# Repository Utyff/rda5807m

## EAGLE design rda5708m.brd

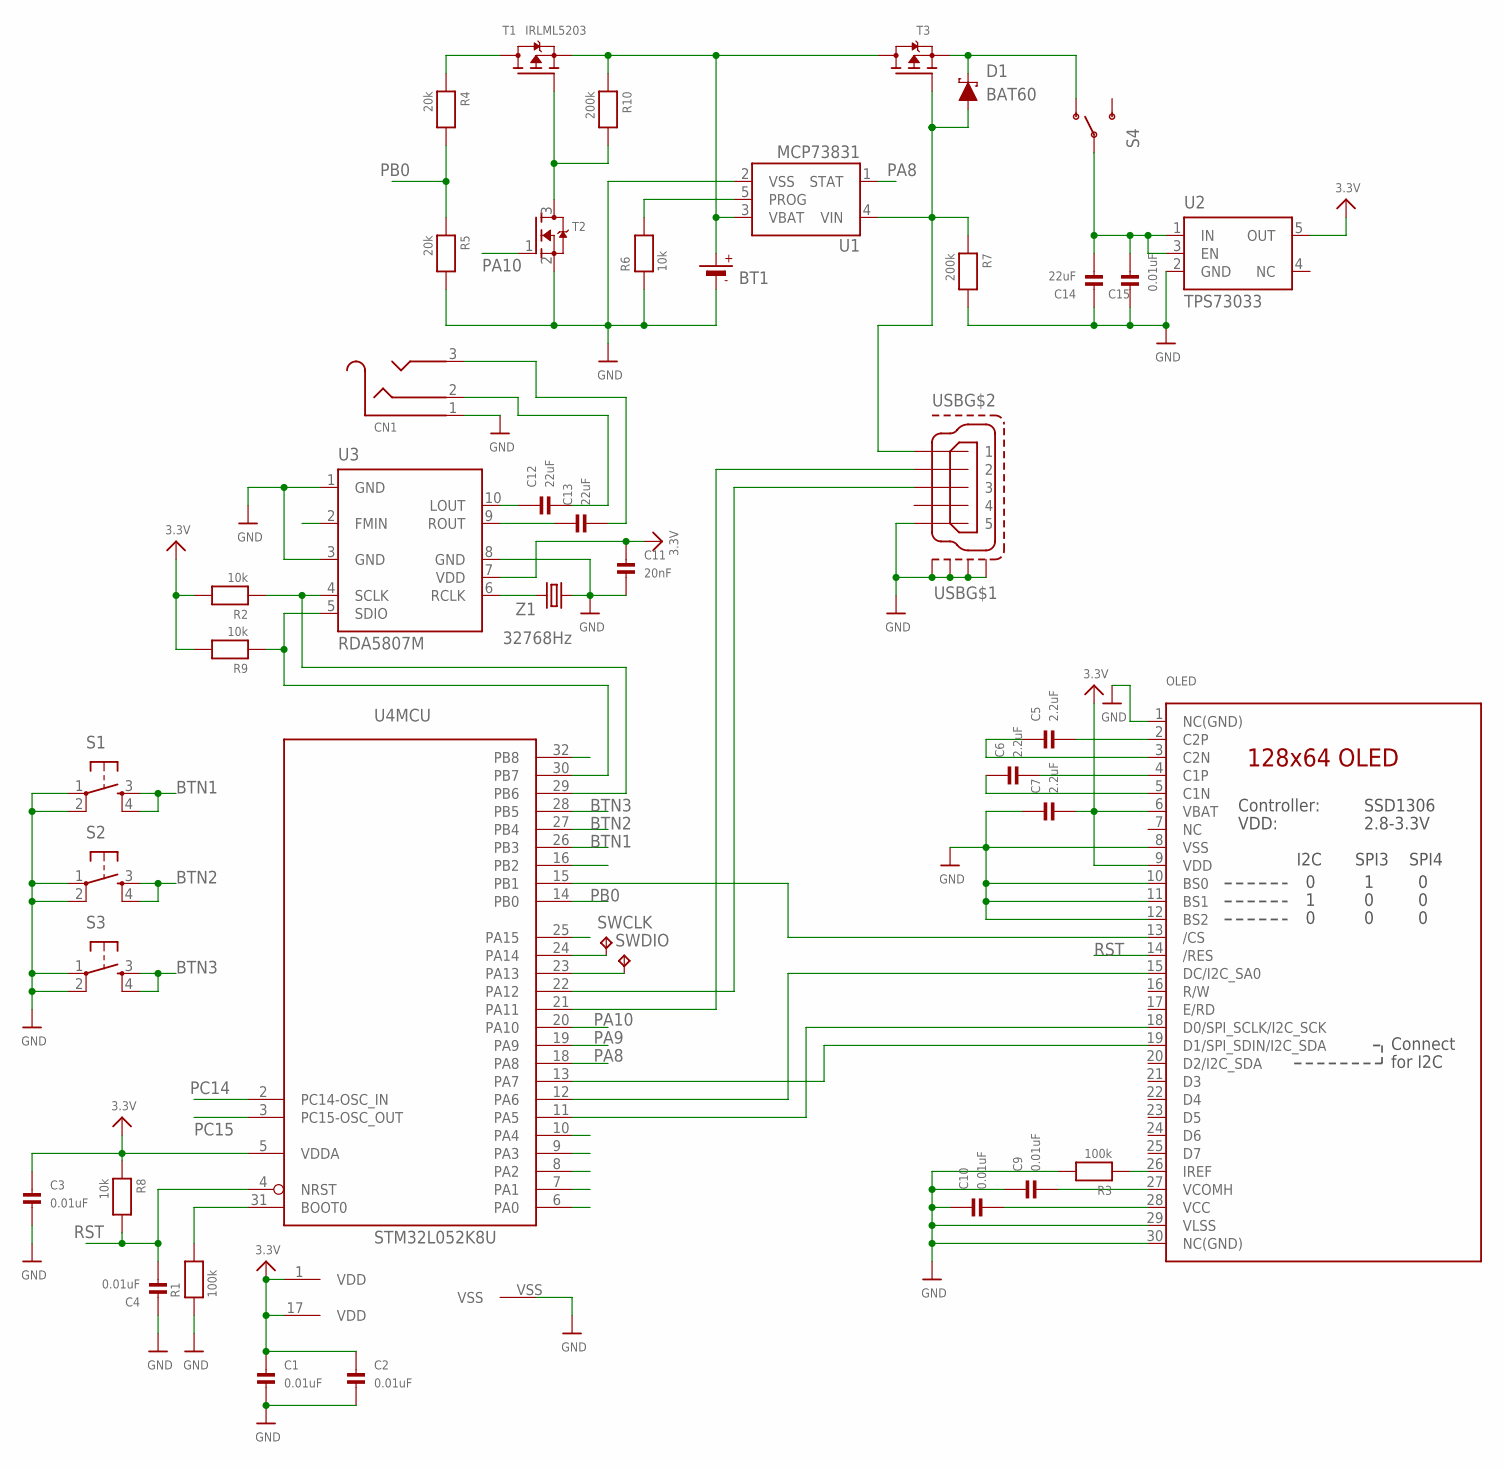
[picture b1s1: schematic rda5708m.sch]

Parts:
BT1: LiPo 4.2V; JSTPH2
C1, C2, C3, C4, C9, C10, C15: 0.01uF; 0603
C5, C6, C7: 2.2uF; 0603
C11: 20nF; 0603
C12, C13, C14: 22uF; 0805
CN1: AUDIO_3.5JACK; AUDIO_3.5
D1: BAT60; SOD-323
OLED: DISP_OLED_UG-2864HSWEG012SIDE; OLED0.96
R1, R3: 100k; 0603
R2, R6, R8, R9: 10k; 0603
R4, R5: 20k; 0603
R7, R10: 200k; 0603
S1, S2, S3: TAC_SWITCH; TACTILE-SWITCH-SMD45
S4: SWITCH-SPDTPTH2; SWITCH-DPDT
SWCLK: TPTP10R; TP10R
SWDIO: TPTP10R; TP10R
T1: IRLML5203; SOT23-R
T2: MOSFET-NREFLOW; SOT23-R
T3: MOSFET-P; SOT23-R
U1: MCP73831; SOT23-5
U2: TPS73033; SOT23-5
U3: RDA5807M; MSOP10
U4: STM32L052K8U; UFQFPN32
USB: MICRO-USB-SHIELD-MICRO_USB-B_4.85_HORN; MICRO_USB-B_4.85_HORN
Z1: 32768Hz; TC26H-SMD

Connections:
3.3V: C1.1, C2.1, C3.1, C7.2, C11.1, OLED.6 (VBAT), OLED.9 (VDD), R2.2, R8.1, R9.2, U2.5 (OUT), U3.7 (VDD), U4.1 (VDD), U4.5 (VDDA), U4.17 (VDD)
+5V: C14.2, C15.2, S4.2, U2.1 (IN), U2.3 (EN)
ANT: U3.2 (FMIN)
BOOT0: R1.2, U4.31 (BOOT0)
BTN1: S1.3, S1.4, U4.26 (PB3)
BTN2: S2.3, S2.4, U4.27 (PB4)
BTN3: S3.3, S3.4, U4.28 (PB5)
GND: BT1.1 (-), C1.2, C2.2, C3.2, C4.2, C7.1, C9.1, C10.1, C11.2, C14.1, C15.1, CN1.1, OLED.1 (NC(GND)), OLED.8 (VSS), OLED.10 (BS0), OLED.11 (BS1), OLED.12 (BS2), OLED.29 (VLSS), OLED.30 (NC(GND)), R1.1, R3.2, R5.2, R6.1, R7.2, S1.1, S1.2, S2.1, S2.2, S3.1, S3.2, T2.2 (S), U1.2 (VSS), U2.2 (GND), U3.1 (GND), U3.3 (GND), U3.8 (GND), U4.VSS, USB.5, USB.M1 (S1), USB.M2 (S2), USB.M3 (S3), USB.M4 (S4), Z1.P$1 (1)
unnamed: U3.6 (RCLK), Z1.P$2 (2)
unnamed: R4.1, T1.3 (D)
unnamed: C12.1, U3.10 (LOUT)
unnamed: C5.2, OLED.2 (C2P)
unnamed: C5.1, OLED.3 (C2N)
unnamed: C6.2, OLED.4 (C1P)
unnamed: C6.1, OLED.5 (C1N)
unnamed: C13.1, U3.9 (ROUT)
unnamed: R6.2, U1.5 (PROG)
unnamed: D1.C, S4.1 (O), T3.2 (S)
unnamed: R10.2, T1.1 (G), T2.3 (D)
unnamed: OLED.26 (IREF), R3.1
unnamed: C9.2, OLED.27 (VCOMH)
unnamed: C10.2, OLED.28 (VCC)
unnamed: C13.2, CN1.3
unnamed: C12.2, CN1.2
PA0: U4.6 (PA0)
PA1: U4.7 (PA1)
PA2: U4.8 (PA2)
PA3: U4.9 (PA3)
PA4: U4.10 (PA4)
PA8: U1.1 (STAT), U4.18 (PA8)
PA9: U4.19 (PA9)
PA10: T2.1 (G), U4.20 (PA10)
PA11: U4.21 (PA11), USB.2
PA12: U4.22 (PA12), USB.3
PA15: U4.25 (PA15)
PB0: R4.2, R5.1, U4.14 (PB0)
PB1: OLED.13 (/CS), U4.15 (PB1)
PB2: U4.16 (PB2)
PB8: U4.32 (PB8)
PC14: U4.2 (PC14-OSC_IN)
PC15: U4.3 (PC15-OSC_OUT)
RST: C4.1, OLED.14 (/RES), R8.2, U4.4 (NRST)
SCLK: R2.1, U3.4 (SCLK), U4.29 (PB6)
SDIO: R9.1, U3.5 (SDIO), U4.30 (PB7)
SPI_DC: OLED.15 (DC/I2C_SA0), U4.12 (PA6)
SPI_MOSI: OLED.19 (D1/SPI_SDIN/I2C_SDA), U4.13 (PA7)
SPI_SCK: OLED.18 (D0/SPI_SCLK/I2C_SCK), U4.11 (PA5)
SWCLK: SWCLK.TP, U4.24 (PA14)
SWDIO: SWDIO.TP, U4.23 (PA13)
VBAT: BT1.2 (+), R10.1, T1.2 (S), T3.3 (D), U1.3 (VBAT)
VUSB: D1.A, R7.1, T3.1 (G), U1.4 (VIN), USB.1

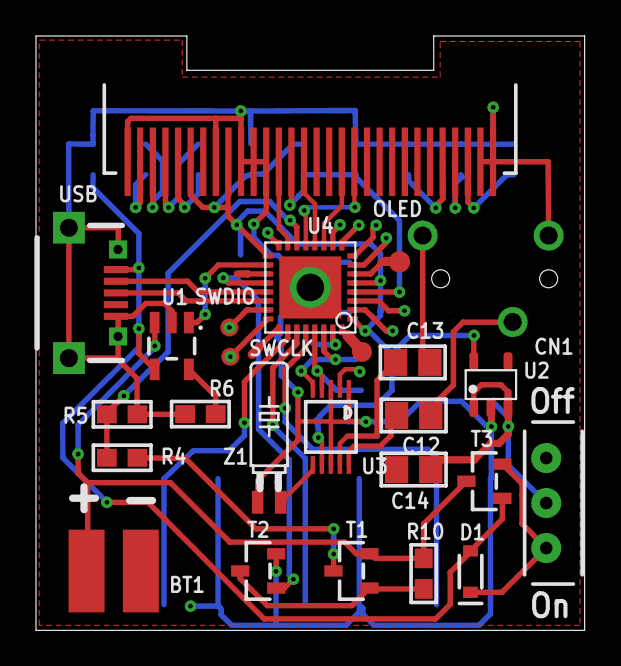
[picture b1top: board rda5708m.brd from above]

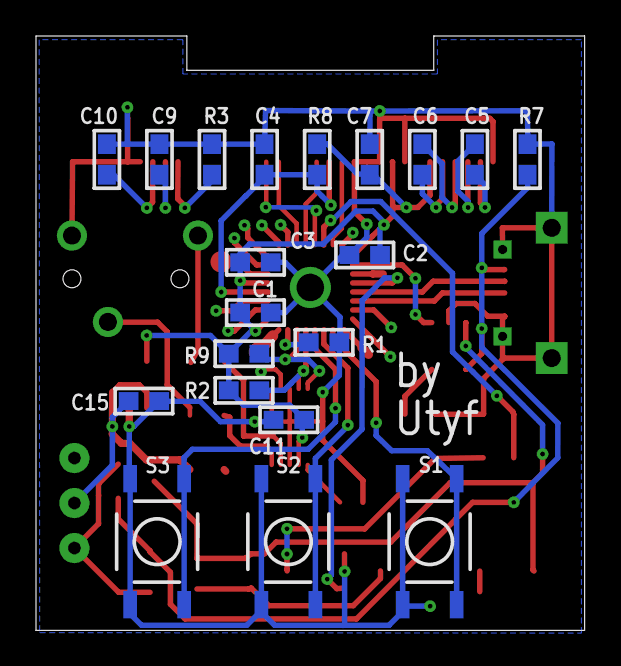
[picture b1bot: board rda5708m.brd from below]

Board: 2 copper layers, 30.5 x 33.0 mm, 43 parts (20 on the bottom side), 39 nets.

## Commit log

2018-08-12 Initial
2018-11-14 fabricated version
2018-11-14 fabricated release
2018-11-14 small update
2018-12-04 pcb fix
2018-12-06 pcb improve

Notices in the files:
parts and their libraries:
microbuilder: This work is placed in the public domain, and may be freely used for commercial and non-commercial work with the following conditions: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
SparkFun-DiscreteSemi: Licensing: Creative Commons ShareAlike 4.0 International - https://creativecommons.org/licenses/by-sa/4.0
